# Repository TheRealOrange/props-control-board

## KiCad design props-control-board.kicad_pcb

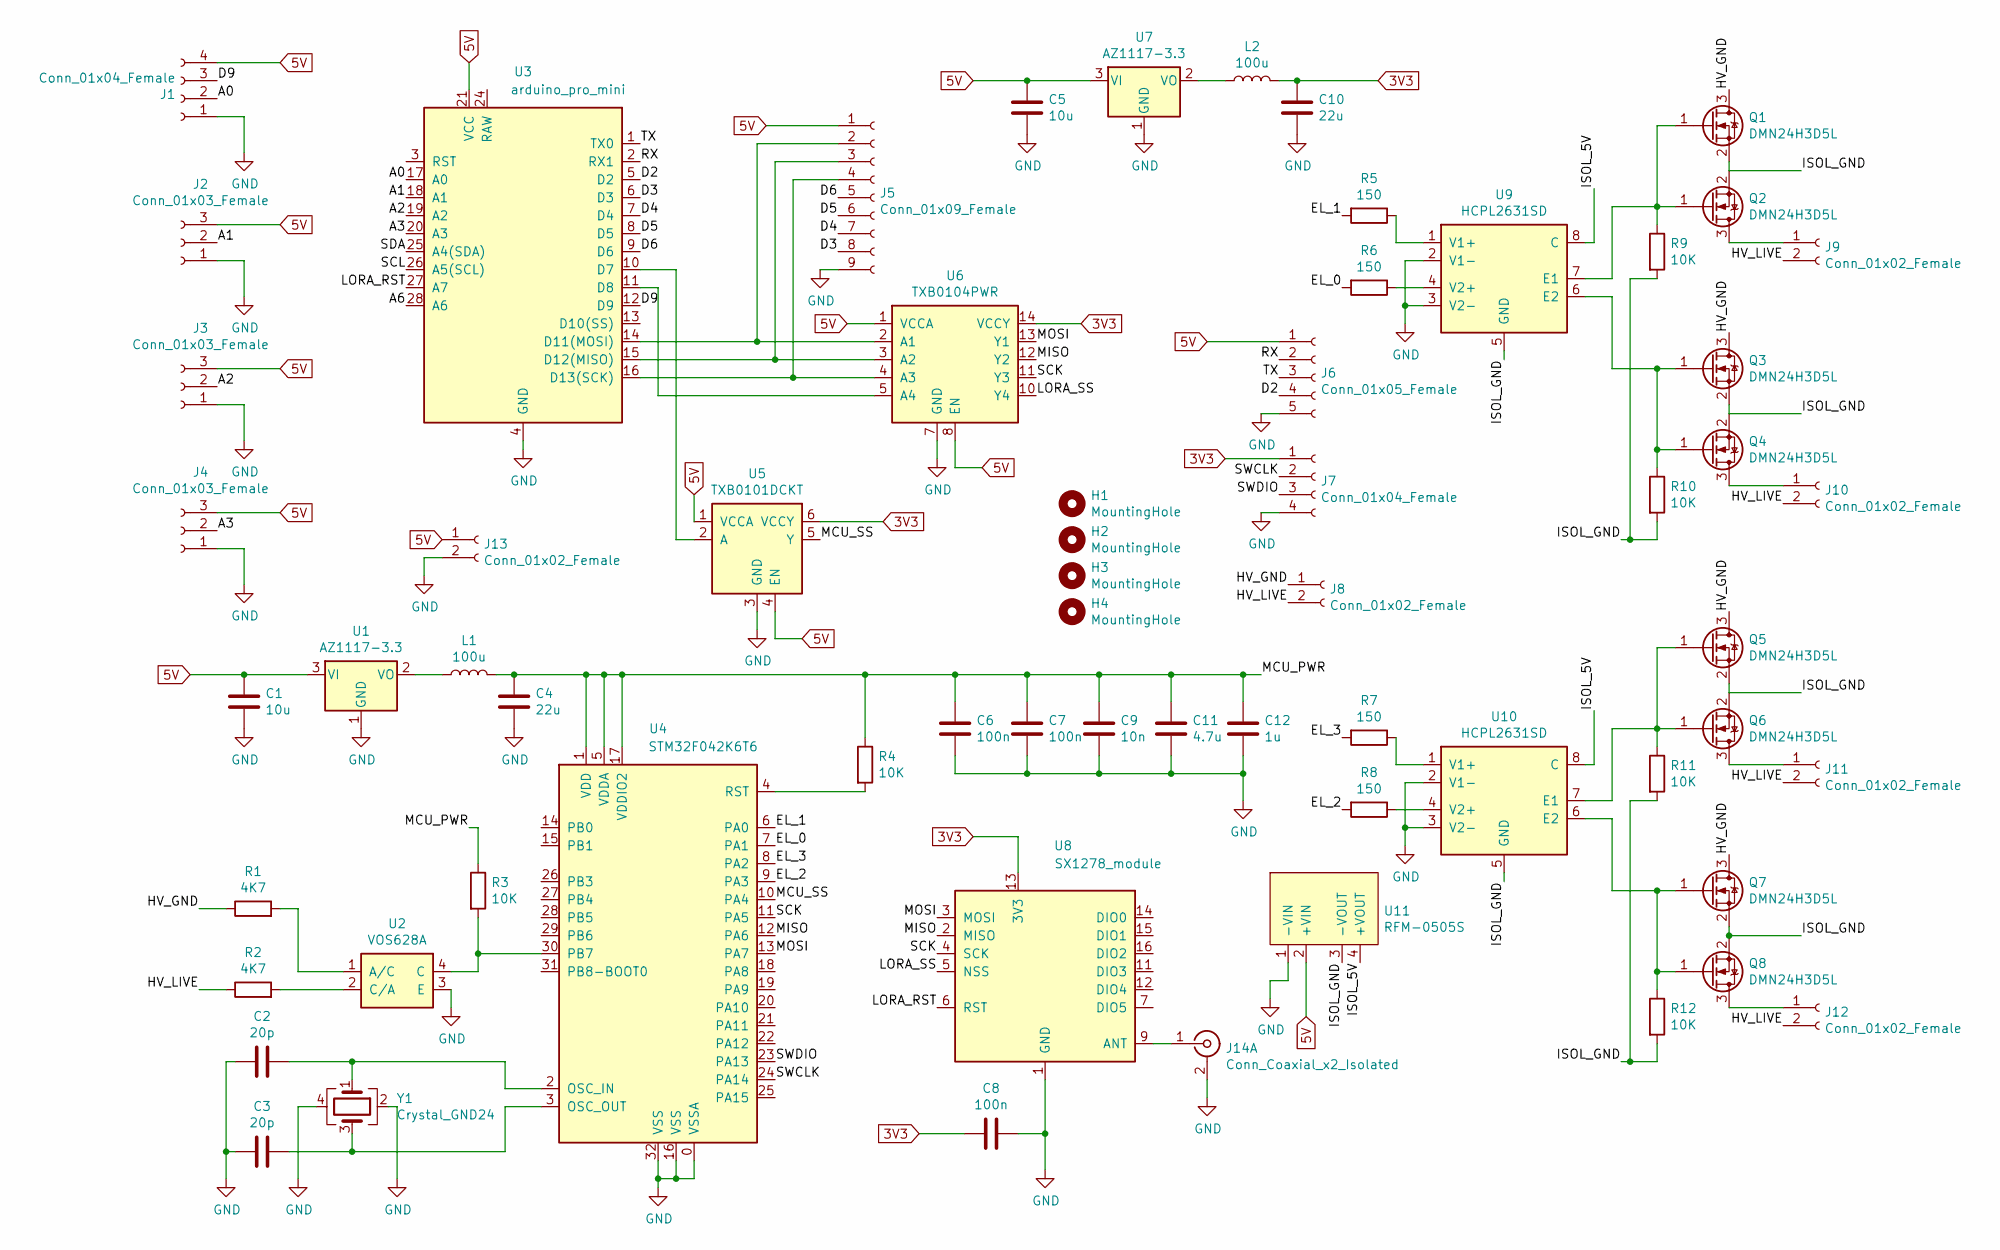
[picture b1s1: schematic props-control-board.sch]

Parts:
C1, C5: 10u; C_0805_2012Metric_Pad1.15x1.40mm_HandSolder; Digikey Part Number 1276-6460-1-ND
C2, C3: 20p; C_0805_2012Metric_Pad1.15x1.40mm_HandSolder; Digikey Part Number 1276-1829-1-ND
C4, C10: 22u; C_0805_2012Metric_Pad1.15x1.40mm_HandSolder; Digikey Part Number 1276-6455-1-ND
C6, C7, C8: 100n; C_0603_1608Metric_Pad1.05x0.95mm_HandSolder; Digikey Part Number 1276-CL10B104KB8NNNLCT-ND
C9: 10n; C_0603_1608Metric_Pad1.05x0.95mm_HandSolder; Digikey Part Number 1276-1009-1-ND
C11: 4.7u; C_0603_1608Metric_Pad1.05x0.95mm_HandSolder; Digikey Part Number 1276-1044-1-ND
C12: 1u; C_0603_1608Metric_Pad1.05x0.95mm_HandSolder; Digikey Part Number 1276-1034-1-ND
H1, H2, H3, H4: MountingHole; MountingHole_3.2mm_M3
J1: Conn_01x04_Female; JST_XH_B4B-XH-A_1x04_P2.50mm_Vertical
J2, J3, J4: Conn_01x03_Female; JST_XH_B3B-XH-A_1x03_P2.50mm_Vertical
J5: Conn_01x09_Female; JST_XH_B9B-XH-A_1x09_P2.50mm_Vertical
J6: Conn_01x05_Female; JST_XH_B5B-XH-A_1x05_P2.50mm_Vertical
J7: Conn_01x04_Female; PinHeader_1x04_P2.54mm_Vertical
J8, J9, J10, J11, J12, J13: Conn_01x02_Female; JST_XH_B2B-XH-A_1x02_P2.50mm_Vertical
J14: Conn_Coaxial_x2_Isolated; U.FL_Hirose_U.FL-R-SMT-1_Vertical
L1, L2: 100u; L_TDK_SLF7045; Digikey Part Number 445-2015-1-ND
Q1, Q2, Q3, Q4, Q5, Q6, Q7, Q8: DMN24H3D5L; SOT-23; Digikey Part Number DMN24H3D5L-7DICT-ND
R1, R2: 4K7; R_1206_3216Metric_Pad1.42x1.75mm_HandSolder; Digikey Part Number RMCF1206JT4K70CT-ND
R3, R4, R9, R10, R11, R12: 10K; R_0805_2012Metric_Pad1.15x1.40mm_HandSolder; Digikey Part Number RNCP0805FTD10K0CT-ND
R5, R6, R7, R8: 150; R_0805_2012Metric_Pad1.15x1.40mm_HandSolder; Digikey Part Number RMCF0805JT150RCT-ND
U1, U7: AZ1117-3.3; SOT-223-3_TabPin2; Digikey Part Number AZ1117CH-3.3TRG1DICT-ND
U2: VOS628A; SOIC-4_4.55x2.6mm_P1.27mm; Digikey Part Number VOS628A-X001TCT-ND
U3: arduino_pro_mini; pro_mini
U4: STM32F042K6T6; LQFP-32_7x7mm_P0.8mm; Digikey Part Number 497-14647-ND
U5: TXB0101DCKT; SOT-363_SC-70-6_Handsoldering; Digikey Part Number 296-32599-1-ND
U6: TXB0104PWR; TSSOP-14_4.4x5mm_P0.65mm; Digikey Part Number 296-21929-1-ND
U8: SX1278_module
U9, U10: HCPL2631SD; SSO-8_6.7x9.8mm_P2.54mm_Clearance8mm; Digikey Part Number HCPL2631SDCT-ND
U11: RFM-0505S; Digikey Part Number 945-3159-ND
Y1: Crystal_GND24; Crystal_SMD_3225-4Pin_3.2x2.5mm_HandSoldering; Digikey Part Number SER4069CT-ND

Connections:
3V3: C8.2, C10.1, J7.1, L2.2, U5.6 (VCCY), U6.14 (VCCY), U8.13 (3V3)
5V: C1.1, C5.1, J1.4, J2.3, J3.3, J4.3, J5.1, J6.1, J13.1, U1.3 (VI), U3.21 (VCC), U5.1 (VCCA), U5.4 (EN), U6.1 (VCCA), U6.8 (EN), U7.3 (VI), U11.2 (+VIN)
/A0: J1.2, U3.17 (A0)
/A1: J2.2, U3.18 (A1)
/A2: J3.2, U3.19 (A2)
/A3: J4.2, U3.20 (A3)
/A6: U3.28 (A6)
/D2: J6.4, U3.5 (D2)
/D3: J5.8, U3.6 (D3)
/D4: J5.7, U3.7 (D4)
/D5: J5.6, U3.8 (D5)
/D6: J5.5, U3.9 (D6)
/D9: J1.3, U3.12 (D9)
/EL_0: R6.2, U4.7 (PA1)
/EL_1: R5.2, U4.6 (PA0)
/EL_2: R8.2, U4.9 (PA3)
/EL_3: R7.2, U4.8 (PA2)
/HV_GND: J8.1, Q1.3 (D), Q3.3 (D), Q5.3 (D), Q7.3 (D), R1.1
/HV_LIVE: J8.2, J9.2, J10.2, J11.2, J12.2, R2.1
/ISOL_5V: U9.8 (C), U10.8 (C), U11.4 (+VOUT)
/ISOL_GND: Q1.2 (S), Q2.2 (S), Q3.2 (S), Q4.2 (S), Q5.2 (S), Q6.2 (S), Q7.2 (S), Q8.2 (S), R9.2, R10.2, R11.2, R12.2, U9.5 (GND), U10.5 (GND), U11.3 (-VOUT)
/LORA_RST: U3.27 (A7), U8.6 (RST)
/LORA_SS: U6.10 (Y4), U8.5 (NSS)
/MCU_PWR: C4.1, C6.1, C7.1, C9.1, C11.1, C12.1, L1.2, R3.1, R4.1, U4.1 (VDD), U4.5 (VDDA), U4.17 (VDDIO2)
/MCU_SS: U4.10 (PA4), U5.5 (Y)
/MISO: U4.12 (PA6), U6.12 (Y2), U8.2 (MISO)
/MOSI: U4.13 (PA7), U6.13 (Y1), U8.3 (MOSI)
/RX: J6.2, U3.2 (RX1)
/SCK: U4.11 (PA5), U6.11 (Y3), U8.4 (SCK)
/SCL: U3.26 (A5(SCL))
/SDA: U3.25 (A4(SDA))
/SWCLK: J7.2, U4.24 (PA14)
/SWDIO: J7.3, U4.23 (PA13)
/TX: J6.3, U3.1 (TX0)
GND: C1.2, C2.2, C3.2, C4.2, C5.2, C6.2, C7.2, C8.1, C9.2, C10.2, C11.2, C12.2, J1.1, J2.1, J3.1, J4.1, J5.9, J6.5, J7.4, J13.2, J14.2 (Ext1), U1.1 (GND), U2.3 (E), U3.4 (GND), U3.23 (GND), U3.29 (GND), U4.0 (VSSA), U4.16 (VSS), U4.32 (VSS), U5.3 (GND), U6.7 (GND), U7.1 (GND), U8.1 (GND), U8.8 (GND), U8.10 (GND), U9.2 (V1-), U9.3 (V2-), U10.2 (V1-), U10.3 (V2-), U11.1 (-VIN), Y1.2, Y1.4
unnamed: C2.1, U4.2 (OSC_IN), Y1.1
unnamed: C3.1, U4.3 (OSC_OUT), Y1.3
unnamed: J5.2, U3.14 (D11(MOSI)), U6.2 (A1)
unnamed: J5.3, U3.15 (D12(MISO)), U6.3 (A2)
unnamed: J5.4, U3.16 (D13(SCK)), U6.4 (A3)
unnamed: J9.1, Q2.3 (D)
unnamed: J10.1, Q4.3 (D)
unnamed: J11.1, Q6.3 (D)
unnamed: J12.1, Q8.3 (D)
unnamed: J14.1 (In1), U8.9 (ANT)
unnamed: L1.1, U1.2 (VO)
unnamed: L2.1, U7.2 (VO)
unnamed: Q1.1 (G), Q2.1 (G), R9.1, U9.7 (E1)
unnamed: Q3.1 (G), Q4.1 (G), R10.1, U9.6 (E2)
unnamed: Q5.1 (G), Q6.1 (G), R11.1, U10.7 (E1)
unnamed: Q7.1 (G), Q8.1 (G), R12.1, U10.6 (E2)
unnamed: R1.2, U2.1 (A/C)
unnamed: R2.2, U2.2 (C/A)
unnamed: R3.2, U2.4 (C), U4.30 (PB7)
unnamed: R4.2, U4.4 (RST)
unnamed: R5.1, U9.1 (V1+)
unnamed: R6.1, U9.4 (V2+)
unnamed: R7.1, U10.1 (V1+)
unnamed: R8.1, U10.4 (V2+)
unnamed: U3.10 (D7), U5.2 (A)
unnamed: U3.11 (D8), U6.5 (A4)
unnamed: U3.3 (RST), U3.22 (RST)
unnamed: U6.6 (NC), U6.9 (NC)

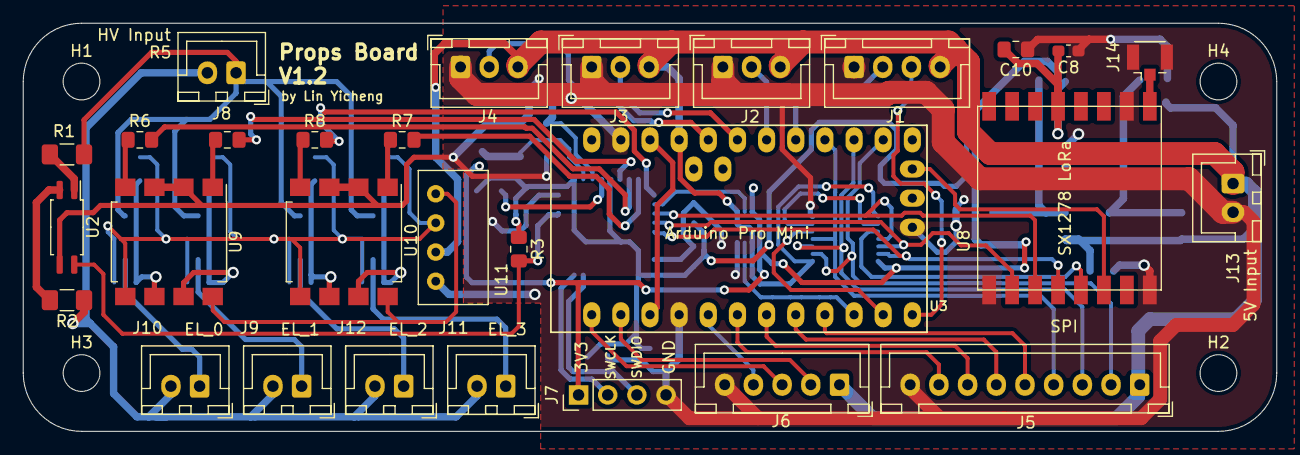
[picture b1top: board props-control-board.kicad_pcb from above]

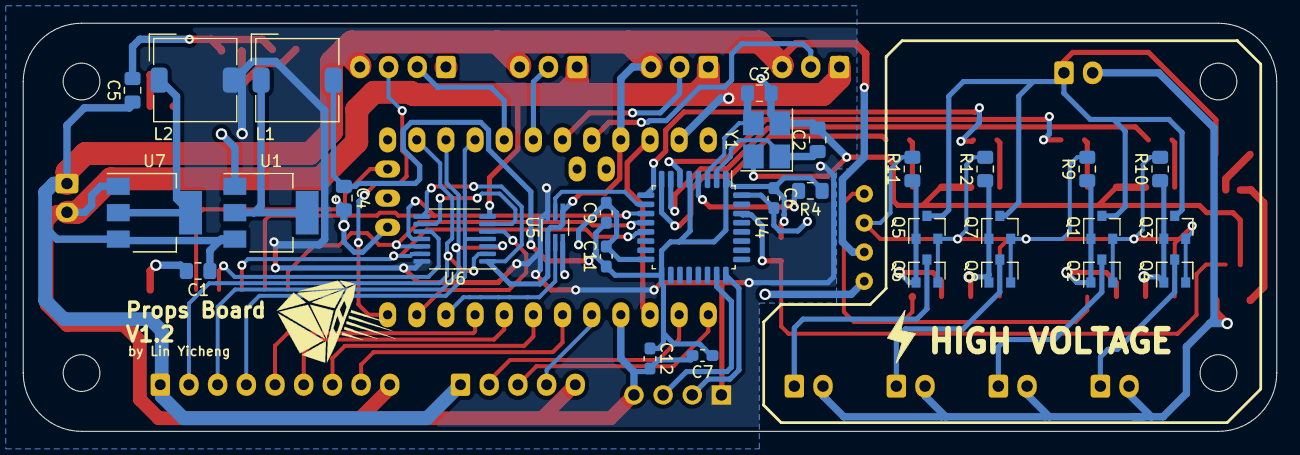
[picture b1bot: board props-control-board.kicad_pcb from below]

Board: 2 copper layers, 109.2 x 35.6 mm, 65 parts (32 on the bottom side), 60 nets.

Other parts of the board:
Ref**: Val**; frontlogo1

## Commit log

2020-11-23 üpdate
2020-11-23 add project files
2020-11-23 expose more GPIO and expose UART
2020-11-27 add 3d models
    Committer: TheRealOrange <linyicheng2004@outlook.com>
2020-11-27 add reset connection to LoRa, add antenna connector
2020-11-27 update pcb
